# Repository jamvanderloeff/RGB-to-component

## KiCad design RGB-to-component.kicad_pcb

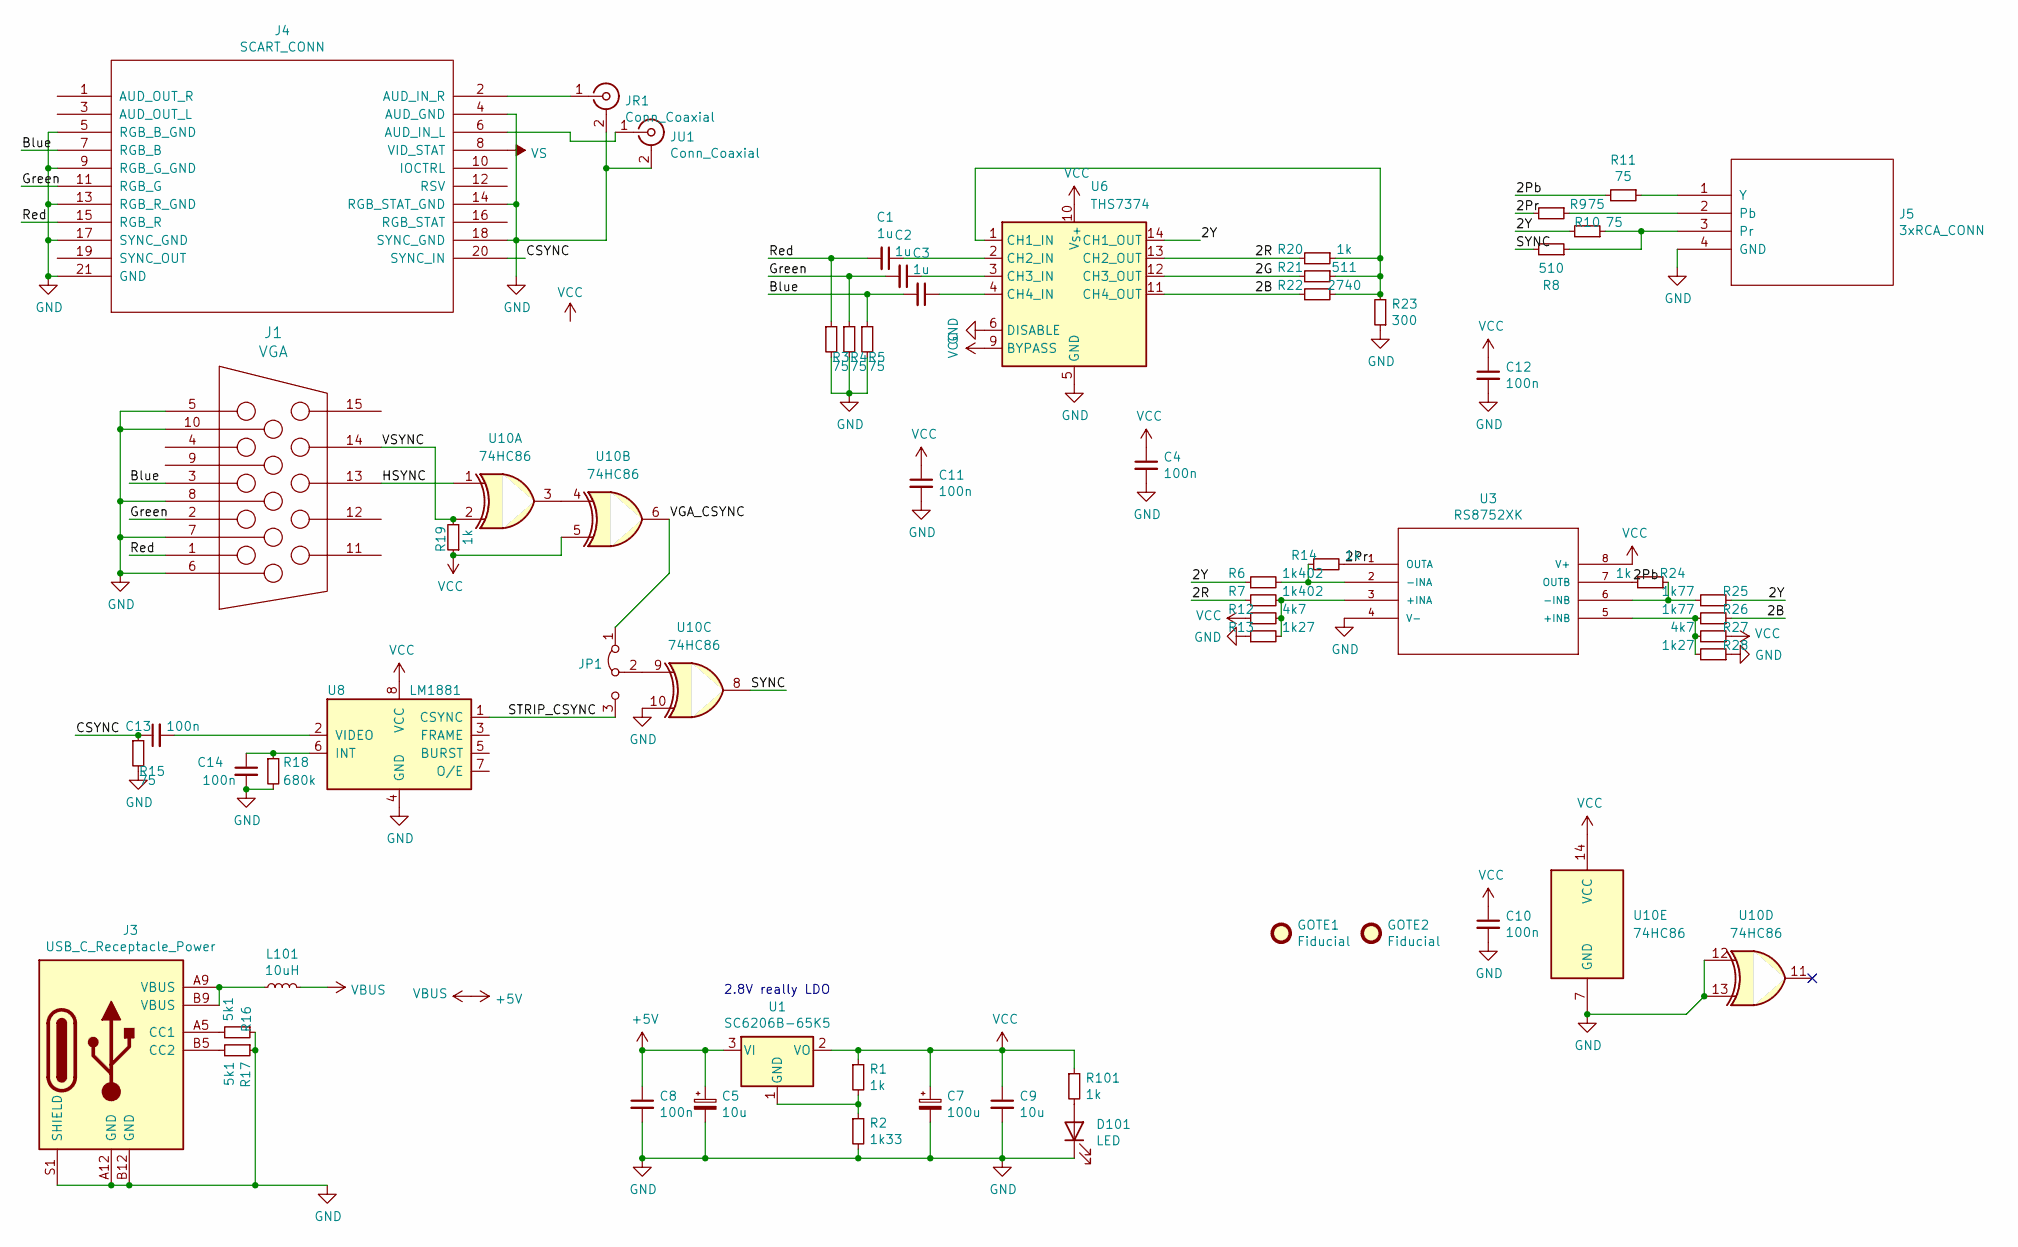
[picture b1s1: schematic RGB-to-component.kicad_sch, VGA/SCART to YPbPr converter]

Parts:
C1, C2, C3: 1u; C_0805_2012Metric_Pad1.15x1.40mm_HandSolder; LCSC C28323
C4, C8, C10, C11, C12, C13, C14: 100n; C_0805_2012Metric_Pad1.15x1.40mm_HandSolder; LCSC C14663
C5: 10u; CP_EIA-3216-18_Kemet-A_Pad1.58x1.35mm_HandSolder; LCSC C7171
C7: 100u; CP_EIA-3528-21_Kemet-B_Pad1.50x2.35mm_HandSolder; LCSC C16133
C9: 10u; C_0805_2012Metric_Pad1.15x1.40mm_HandSolder; LCSC C15850
D101: LED; LED_0805_2012Metric; LCSC C34499
GOTE1: Fiducial; uwuriel; LCSC NOT FITTED
GOTE2: Fiducial; borgar; LCSC NOT FITTED
J1: VGA; VGA_CONN; LCSC NOT FITTED
J3: USB_C_Receptacle_Power; USB_C_Receptacle_Generic_Power_Only; LCSC C283540
J4: SCART_CONN; LCSC NOT FITTED
J5: 3xRCA_CONN; 3xRCA_CONN_SINGLE; LCSC NOT FITTED
JP1: Jumper_3_Bridged12; SolderJumper-3_P1.3mm_Bridged12_Pad1.0x1.5mm; LCSC NOT FITTED
JR1: Conn_Coaxial; Cheapo_RCA_single_edge; LCSC NOT FITTED
JU1: Conn_Coaxial; Cheapo_RCA_single_edge; LCSC NOT FITTED
L101: 10uH; L_0805_2012Metric_Pad1.15x1.40mm_HandSolder; LCSC C1046
R1, R14, R19, R20, R24, R101: 1k; R_0805_2012Metric_Pad1.15x1.40mm_HandSolder; LCSC C17513
R2: 1k33; R_0805_2012Metric_Pad1.15x1.40mm_HandSolder; LCSC C17382
R3, R4, R5, R9, R10, R11, R15: 75; R_0805_2012Metric_Pad1.15x1.40mm_HandSolder; LCSC C17820
R6, R7: 1k402; R_0805_2012Metric_Pad1.15x1.40mm_HandSolder; LCSC C17388
R8: 510; R_0805_2012Metric_Pad1.15x1.40mm_HandSolder; LCSC C17734
R12, R27: 4k7; R_0805_2012Metric_Pad1.15x1.40mm_HandSolder; LCSC C17673
R13, R28: 1k27; R_0805_2012Metric_Pad1.15x1.40mm_HandSolder; LCSC C101451
R16, R17: 5k1; R_0805_2012Metric_Pad1.15x1.40mm_HandSolder; LCSC C27834
R18: 680k; R_0805_2012Metric_Pad1.15x1.40mm_HandSolder; LCSC C17797
R21: 511; R_0805_2012Metric_Pad1.15x1.40mm_HandSolder; LCSC C17736
R22: 2740; R_0805_2012Metric_Pad1.15x1.40mm_HandSolder; LCSC C322392
R23: 300; R_0805_2012Metric_Pad1.15x1.40mm_HandSolder; LCSC C17617
R25, R26: 1k77; R_0805_2012Metric_Pad1.15x1.40mm_HandSolder; LCSC C17397
U1: SC6206B-65K5; SOT-23; LCSC C130827
U3: RS8752XK; SOIC-8_3.9x4.9mm_P1.27mm; LCSC C236994
U6: THS7374; TSSOP-14_4.4x5mm_P0.65mm; LCSC C2652746
U8: LM1881; SOIC-8_3.9x4.9mm_P1.27mm; LCSC C518922
U10: 74HC86; TSSOP-14_4.4x5mm_P0.65mm

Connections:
+5V: C5.1, C8.1, L101.2, U1.3 (VI)
/2B: R22.2, R26.1, U6.11 (CH4_OUT)
/2G: R21.2, U6.12 (CH3_OUT)
/2Pb: R11.2, R24.2, U3.7 (OUTB)
/2Pr: R9.2, R14.2, U3.1 (OUTA)
/2R: R7.1, R20.2, U6.13 (CH2_OUT)
/2Y: R6.1, R10.2, R25.1, U6.14 (CH1_OUT)
/Blue: C3.2, J1.3 (BLUE), J4.7 (RGB_B), R5.1
/CSYNC: C13.1, J4.20 (SYNC_IN), R15.1
/Green: C2.2, J1.2 (GREEN), J4.11 (RGB_G), R4.1
/HSYNC: J1.13 (HSYNC), U10.1
/Red: C1.2, J1.1 (RED), J4.15 (RGB_R), R3.1
/STRIP_CSYNC: JP1.3 (B), U8.1 (CSYNC)
/SYNC: R8.2, U10.8
/VGA_CSYNC: JP1.1 (A), U10.6
/VSYNC: J1.14 (VSYNC), R19.2, U10.2
GND: C4.2, C5.2, C7.2, C8.2, C9.2, C10.2, C11.2, C12.2, C14.2, D101.1 (K), J1.5 (GND_HSYNC), J1.6 (RED_RTN), J1.7 (GREEN_RTN), J1.8 (BLUE_RTN), J1.10 (GND_VSYNC), J3.A12 (GND), J3.B12 (GND), J3.S1 (SHIELD), J4.4 (AUD_GND), J4.5 (RGB_B_GND), J4.9 (RGB_G_GND), J4.13 (RGB_R_GND), J4.14 (RGB_STAT_GND), J4.17 (SYNC_GND), J4.18 (SYNC_GND), J4.21 (GND), J5.4 (GND), JR1.2 (Ext), JU1.2 (Ext), R2.2, R3.2, R4.2, R5.2, R13.1, R15.2, R16.1, R17.1, R18.2, R23.1, R28.1, U3.4 (V-), U6.5 (GND), U6.6 (DISABLE), U8.4 (GND), U10.7 (GND), U10.10, U10.12, U10.13
unnamed: D101.2 (A), R101.2
unnamed: J3.A5 (CC1), R16.2
unnamed: J3.B5 (CC2), R17.2
unnamed: J3.A9 (VBUS), J3.B9 (VBUS), L101.1
unnamed: J4.6 (AUD_IN_L), JU1.1 (In)
unnamed: J4.2 (AUD_IN_R), JR1.1 (In)
unnamed: J5.2 (Pb), R9.1
unnamed: J5.3 (Pr), R8.1, R10.1
unnamed: J5.1 (Y), R11.1
unnamed: JP1.2 (C), U10.9
unnamed: R1.2, R2.1, U1.1 (GND)
unnamed: R7.2, R12.2, R13.2, U3.3 (+INA)
unnamed: R26.2, R27.2, R28.2, U3.5 (+INB)
unnamed: R6.2, R14.1, U3.2 (-INA)
unnamed: R24.1, R25.2, U3.6 (-INB)
unnamed: R20.1, R21.1, R22.1, R23.2, U6.1 (CH1_IN)
unnamed: C1.1, U6.2 (CH2_IN)
unnamed: C2.1, U6.3 (CH3_IN)
unnamed: C3.1, U6.4 (CH4_IN)
unnamed: C14.1, R18.1, U8.6 (INT)
unnamed: C13.2, U8.2 (VIDEO)
unnamed: U10.3, U10.4
VCC: C4.1, C7.1, C9.1, C10.1, C11.1, C12.1, R1.1, R12.1, R19.1, R27.1, R101.1, U1.2 (VO), U3.8 (V+), U6.9 (BYPASS), U6.10 (V_{S+}), U8.8 (VCC), U10.5, U10.14 (VCC)
VS: J4.8 (VID_STAT)

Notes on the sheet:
2.8V really LDO

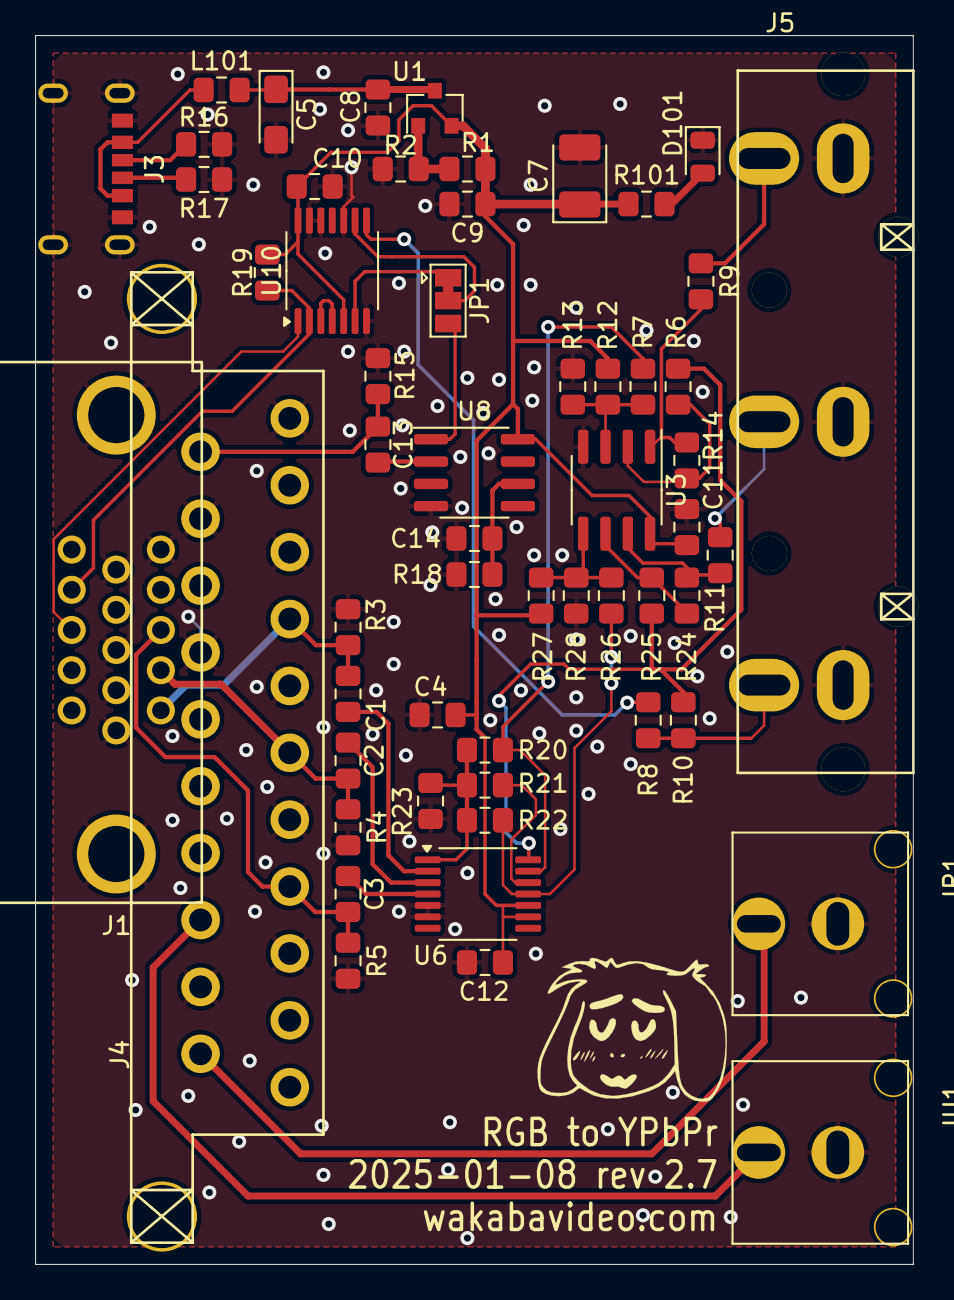
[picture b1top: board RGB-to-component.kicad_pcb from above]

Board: 2 copper layers, 50.0 x 70.0 mm, 58 parts (1 on the bottom side), 40 nets.

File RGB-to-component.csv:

Comment,Designator,Footprint,LCSC, LCSC
"1u","C1,C2,C3","Capacitor_SMD:C_0805_2012Metric_Pad1.15x1.40mm_HandSolder","","C28323"
"100n","C4,C8,C10,C11,C12,C13,C14","Capacitor_SMD:C_0805_2012Metric_Pad1.15x1.40mm_HandSolder","","C14663"
"10u","C5","Capacitor_Tantalum_SMD:CP_EIA-3216-18_Kemet-A_Pad1.58x1.35mm_HandSolder",""," C16133"
"100u","C7","Capacitor_Tantalum_SMD:CP_EIA-3528-21_Kemet-B_Pad1.50x2.35mm_HandSolder",""," C16133"
"10u","C9","Capacitor_SMD:C_0805_2012Metric_Pad1.15x1.40mm_HandSolder","","C15850"
"LED","D101","LED_SMD:LED_0805_2012Metric","","C34499"
"Fiducial","GOTE1","videobits:uwuriel","","NOT FITTED"
"Fiducial","GOTE2","videobits:borgar","","NOT FITTED"
"VGA","J1","custom_components:VGA_CONN","","NOT FITTED"
"USB_C_Receptacle_Power","J3","videobits:USB_C_Receptacle_Generic_Power_Only","","C283540"
"SCART_CONN","J4","custom_components:SCART_CONN","","NOT FITTED"
"3xRCA_CONN","J5","videobits:3xRCA_CONN_SINGLE","","NOT FITTED"
"Jumper_3_Bridged12","JP1","Jumper:SolderJumper-3_P1.3mm_Bridged12_Pad1.0x1.5mm","","NOT FITTED"
"Conn_Coaxial","JR1,JU1","videobits:Cheapo_RCA_single_edge","","NOT FITTED"
"10u","L101","Inductor_SMD:L_0805_2012Metric_Pad1.15x1.40mm_HandSolder","","C1046"
"1k","R1,R14,R19,R20,R24,R101","Resistor_SMD:R_0805_2012Metric_Pad1.15x1.40mm_HandSolder","","C17513"
"4k7","R12,R27","Resistor_SMD:R_0805_2012Metric_Pad1.15x1.40mm_HandSolder","","C17673"
"1k27","R13,R28","Resistor_SMD:R_0805_2012Metric_Pad1.15x1.40mm_HandSolder","","C40880"
"5k1","R16,R17","Resistor_SMD:R_0805_2012Metric_Pad1.15x1.40mm_HandSolder","","C27834"
"680k","R18","Resistor_SMD:R_0805_2012Metric_Pad1.15x1.40mm_HandSolder","","C17797"
"1k33","R2","Resistor_SMD:R_0805_2012Metric_Pad1.15x1.40mm_HandSolder","","C17382"
"511","R21","Resistor_SMD:R_0805_2012Metric_Pad1.15x1.40mm_HandSolder","","C273884"
"2740","R22","Resistor_SMD:R_0805_2012Metric_Pad1.15x1.40mm_HandSolder","","C26009"
"300","R23","Resistor_SMD:R_0805_2012Metric_Pad1.15x1.40mm_HandSolder","","C17617"
"1k77","R25,R26","Resistor_SMD:R_0805_2012Metric_Pad1.15x1.40mm_HandSolder","","C17397"
"75","R3,R4,R5,R9,R10,R11,R15","Resistor_SMD:R_0805_2012Metric_Pad1.15x1.40mm_HandSolder","","C20638"
"1k402","R6,R7","Resistor_SMD:R_0805_2012Metric_Pad1.15x1.40mm_HandSolder","","C17388"
"510","R8","Resistor_SMD:R_0805_2012Metric_Pad1.15x1.40mm_HandSolder","","C17734"
"SC6206B-65K5","U1","Package_TO_SOT_SMD:SOT-23","","C130827"
"TPF141-TR","U2,U4,U5,U9","Package_TO_SOT_SMD:SOT-23-6_Handsoldering","","C155440"
"RS8752XK","U3","Package_SO:SOIC-8_3.9x4.9mm_P1.27mm","","C236994"
"74AHCT1G86","U6,U7","Package_TO_SOT_SMD:SOT-23-5","","C43417"
"LM1881","U8","Package_SO:SOIC-8_3.9x4.9mm_P1.27mm","","C518922"

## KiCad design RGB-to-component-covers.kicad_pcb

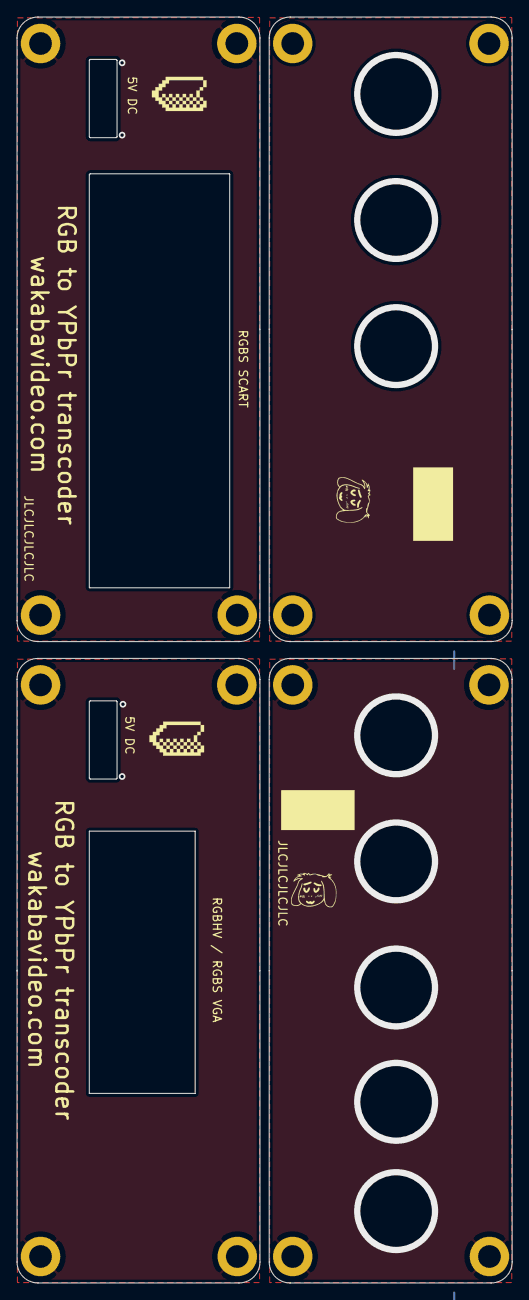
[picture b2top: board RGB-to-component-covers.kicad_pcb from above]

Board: 2 copper layers, 58.9 x 150.5 mm, 16 parts (0 on the bottom side), 3 nets.

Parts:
H1, H3, H4, H4#2, H5, H7, H8, H8#2, H9, H11, H12, H12#2, H13, H15, H16, H16#2: MountingHole_Pad; MountingHole_2.7mm_M2.5_DIN965_Pad

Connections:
/GND1: H1.1, H5.1, H9.1, H13.1
/GND3: H3.1, H7.1, H11.1, H15.1
/GND4: H4.1, H8.1, H12.1, H16.1

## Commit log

2020-04-04 updated gerber
2020-06-11 reusing video amp, ferrite, power led, updated jlc files
2020-06-11 starting panelise
2020-06-26 fixed resistor
2020-11-01 changed RCA jacks to single centre pin style, AHCT gates for VGA sync
2021-05-09 sync commit
2021-05-09 swapped opamp for SOIC package
2021-09-02 add single panel assembly file
2021-09-02 add single panel gerb zip
2021-09-23 add the cover plates
2021-11-13 i am bad at git
2021-11-27 covers gerb for vga/shart->component
2022-08-06 converting to kicad 6
2022-09-09 return to THS7374 (temporary single board only)
2022-09-09 updates single gerbs with THS7374
2022-09-16 gerbs update
2022-11-10 swapping video amps again to TPF141 for JLC availability
2023-01-06 covers updated
2023-07-29 updated to kicad 7
2023-07-30 folder cleanup
2023-12-26 kicad update, oscillator footprint replaced
2024-01-10 75 ohm removed from hsync, only terminates scart's csync
2024-05-23 buffer csync stripper, logic moved to single chip
2024-05-23 prod files
2024-05-23 remember to save the schematic too
2025-01-07 change back to THS7374
2025-01-07 swap to THS7374, updated parts
